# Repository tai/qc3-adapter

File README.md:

# QC3.0 to 3.6-20V DC adapter

This adapter controls USB QC3.0 adapters/batteries to generate DC output of 3.6-20V.
Actual output voltage range depends on capability of power source, and it seems most supports 3.6-12V range.

Unlike USB-PD, QC3.0 power source is quite easy to control.
All you need is to control USB D+/D- lines to appropriate level, and send a pulse to raise/lower the output voltage.

# Note on KiCad

Although KiCad v5 is out, this design uses KiCad v4.
KiCad v5 seems to have a library loading issue that stalls whenever I try to load parts model/footprint.
This is really a deal breaker.

# Note on JLCPCB

I'm using JLCPCB to manifacture the board.

To submit the order to [JLCPCB](https://jlcpcb.com/), follow the instruction in the page below:

> How to export Kicad PCB to gerber files
> - https://support.jlcpcb.com/article/44-how-to-export-kicad-pcb-to-gerber-files

> PCB Panelization
- https://support.jlcpcb.com/article/49-pcb-panelization

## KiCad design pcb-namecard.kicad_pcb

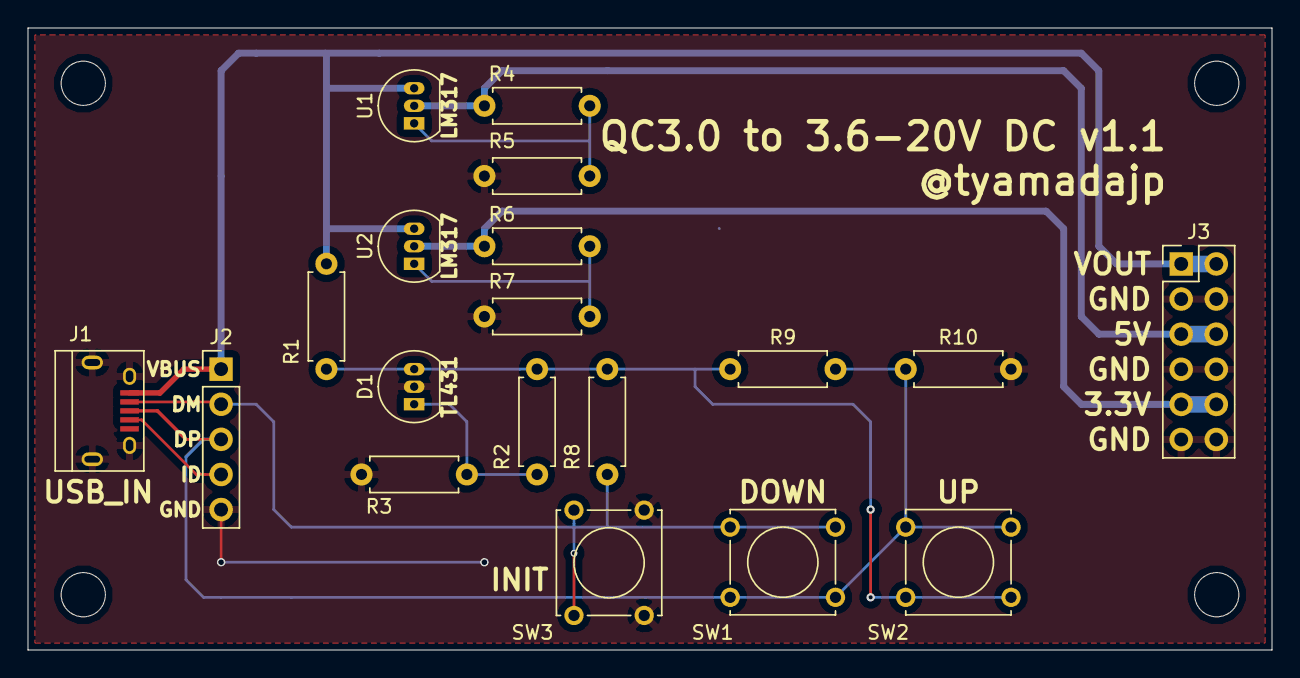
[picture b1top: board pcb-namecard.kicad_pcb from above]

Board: 2 copper layers, 90.0 x 45.0 mm, 23 parts (0 on the bottom side), 11 nets.

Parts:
D1: TL431; TO-92_Inline_Narrow_Oval
J1: USB_OTG; USB_Micro-B
J2: USB_ALT; Pin_Header_Straight_1x05_Pitch2.54mm
J3: POWER_OUT; Pin_Header_Straight_2x06_Pitch2.54mm
MH1, MH2, MH3, MH4: M3; MountingHole_3.2mm_M3
R1: 100; R_Axial_DIN0207_L6.3mm_D2.5mm_P7.62mm_Horizontal
R2, R10: 3.3K; R_Axial_DIN0207_L6.3mm_D2.5mm_P7.62mm_Horizontal
R3, R8, R9: 10K; R_Axial_DIN0207_L6.3mm_D2.5mm_P7.62mm_Horizontal
R4, R7: 330; R_Axial_DIN0207_L6.3mm_D2.5mm_P7.62mm_Horizontal
R5: 1K; R_Axial_DIN0207_L6.3mm_D2.5mm_P7.62mm_Horizontal
R6: 220; R_Axial_DIN0207_L6.3mm_D2.5mm_P7.62mm_Horizontal
SW1: DOWN; SW_Tactile_Straight_KSA0Axx1LFTR
SW2: UP; SW_Tactile_Straight_KSA0Axx1LFTR
SW3: INIT; SW_Tactile_Straight_KSA0Axx1LFTR
U1, U2: LM317; TO-92_Inline_Narrow_Oval

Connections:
GND: D1.2, J1.5, J1.6, J2.5, J3.3, J3.4, J3.7, J3.8, J3.11, J3.12, R3.2, R5.2, R7.2, R10.2, SW3.2
unnamed: D1.1, R2.2, R3.1
unnamed: D1.3, R1.2, R2.1, R8.1, R9.1, SW2.2
unnamed: J1.1, J2.1, J3.1, J3.2, R1.1, U1.3, U2.3
unnamed: J1.2, J2.2, R8.2, SW1.1, SW3.1
unnamed: J1.3, J2.3, R9.2, R10.1, SW1.2, SW2.1
unnamed: J1.4, J2.4
unnamed: J3.5, J3.6, R4.1, U1.2
unnamed: J3.9, J3.10, R6.1, U2.2
unnamed: R4.2, R5.1, U1.1
unnamed: R6.2, R7.1, U2.1

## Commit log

2019-08-21 - Backported to KiCad v4 - Added INIT button to enter QC3.0 mode - Revised register values
2019-08-21 Added panelized PCB
2019-08-21 Added README
2019-08-29 Changed USB_ALT to 01x05 connector, with independent ID pin.
2019-08-29 - Changed USB_ALT to 01x05 connector. - Added more text to F.Silk
2019-08-30 Renamed project
